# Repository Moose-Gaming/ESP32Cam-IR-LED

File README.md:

# ESP32Cam-IR-LED

***This Board makes your ESP32Cam see in the dark using 24 IR LEDs!***

In this repo, you will find the Gerber files required for ordering the PCB, as well as the KiCAD project files for editing the model (KiCAD 7.0 and later).
The archive folder holds all my previous .stl files.

The [**Wiki**](https://github.com/Moose-Gaming/ESP32Cam-IR-LED/wiki) should guide you through successfully ordering and assembling the PCB.

Check out [**my other projects**](https://github.com/Moose-Gaming/)!

***

# License
<br /> The ESP32Cam IR LED by MooseGaming is licensed under a <a rel="license" href="http://creativecommons.org/licenses/by-nc-sa/4.0/">Creative Commons Attribution-NonCommercial-ShareAlike 4.0 International License</a>.

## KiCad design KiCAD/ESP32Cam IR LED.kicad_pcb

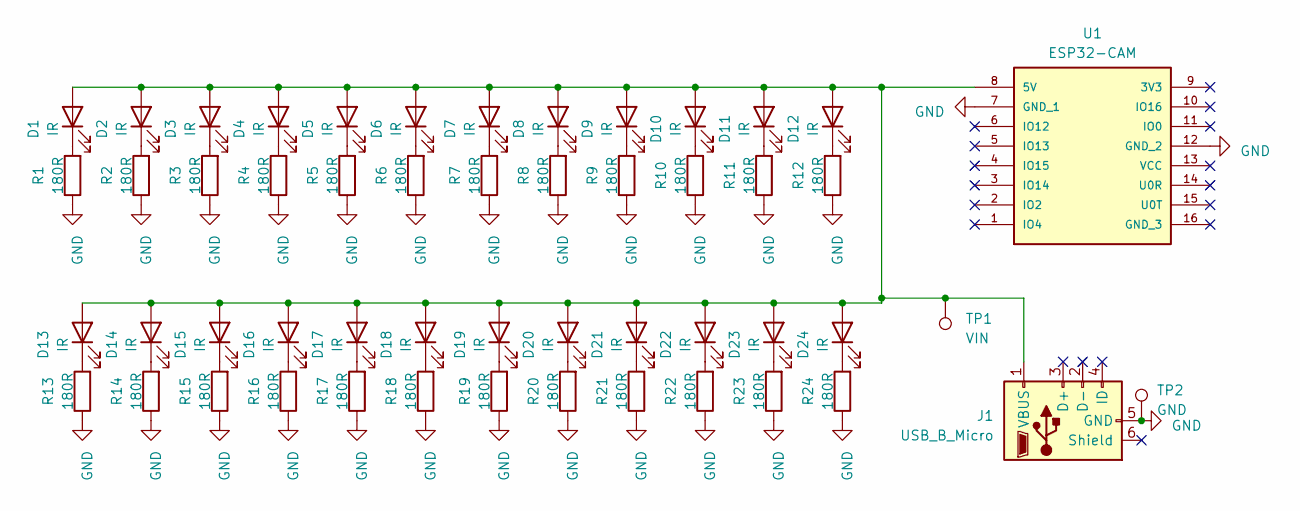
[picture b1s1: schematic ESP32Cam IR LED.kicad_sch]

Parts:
D1, D2, D3, D4, D5, D6, D7, D8, D9, D10, D11, D12, D13, D14, D15, D16, D17, D18, D19, D20, D21, D22, D23, D24: IR; LED_D3.0mm
J1: USB_B_Micro; USB_Micro-B_Wuerth_629105150521
R1, R2, R3, R4, R5, R6, R7, R8, R9, R10, R11, R12, R13, R14, R15, R16, R17, R18, R19, R20, R21, R22, R23, R24: 180R; R_0603_1608Metric
TP1: VIN; TestPoint_Pad_D2.0mm
TP2: GND; TestPoint_Pad_D2.0mm
U1: ESP32-CAM; MANUFACTURER_PART_NUMBER ESP32-CAM

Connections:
GND: J1.5 (GND), R1.1, R2.1, R3.1, R4.1, R5.1, R6.1, R7.1, R8.1, R9.1, R10.1, R11.1, R12.1, R13.1, R14.1, R15.1, R16.1, R17.1, R18.1, R19.1, R20.1, R21.1, R22.1, R23.1, R24.1, TP2.1, U1.7 (GND_1), U1.12 (GND_2)
unnamed: D1.2 (A), D2.2 (A), D3.2 (A), D4.2 (A), D5.2 (A), D6.2 (A), D7.2 (A), D8.2 (A), D9.2 (A), D10.2 (A), D11.2 (A), D12.2 (A), D13.2 (A), D14.2 (A), D15.2 (A), D16.2 (A), D17.2 (A), D18.2 (A), D19.2 (A), D20.2 (A), D21.2 (A), D22.2 (A), D23.2 (A), D24.2 (A), J1.1 (VBUS), TP1.1, U1.8 (5V)
unnamed: D1.1 (K), R1.2
unnamed: D2.1 (K), R2.2
unnamed: D3.1 (K), R3.2
unnamed: D4.1 (K), R4.2
unnamed: D5.1 (K), R5.2
unnamed: D6.1 (K), R6.2
unnamed: D7.1 (K), R7.2
unnamed: D8.1 (K), R8.2
unnamed: D9.1 (K), R9.2
unnamed: D10.1 (K), R10.2
unnamed: D11.1 (K), R11.2
unnamed: D12.1 (K), R12.2
unnamed: D13.1 (K), R13.2
unnamed: D14.1 (K), R14.2
unnamed: D15.1 (K), R15.2
unnamed: D16.1 (K), R16.2
unnamed: D17.1 (K), R17.2
unnamed: D18.1 (K), R18.2
unnamed: D19.1 (K), R19.2
unnamed: D20.1 (K), R20.2
unnamed: D21.1 (K), R21.2
unnamed: D22.1 (K), R22.2
unnamed: D23.1 (K), R23.2
unnamed: D24.1 (K), R24.2

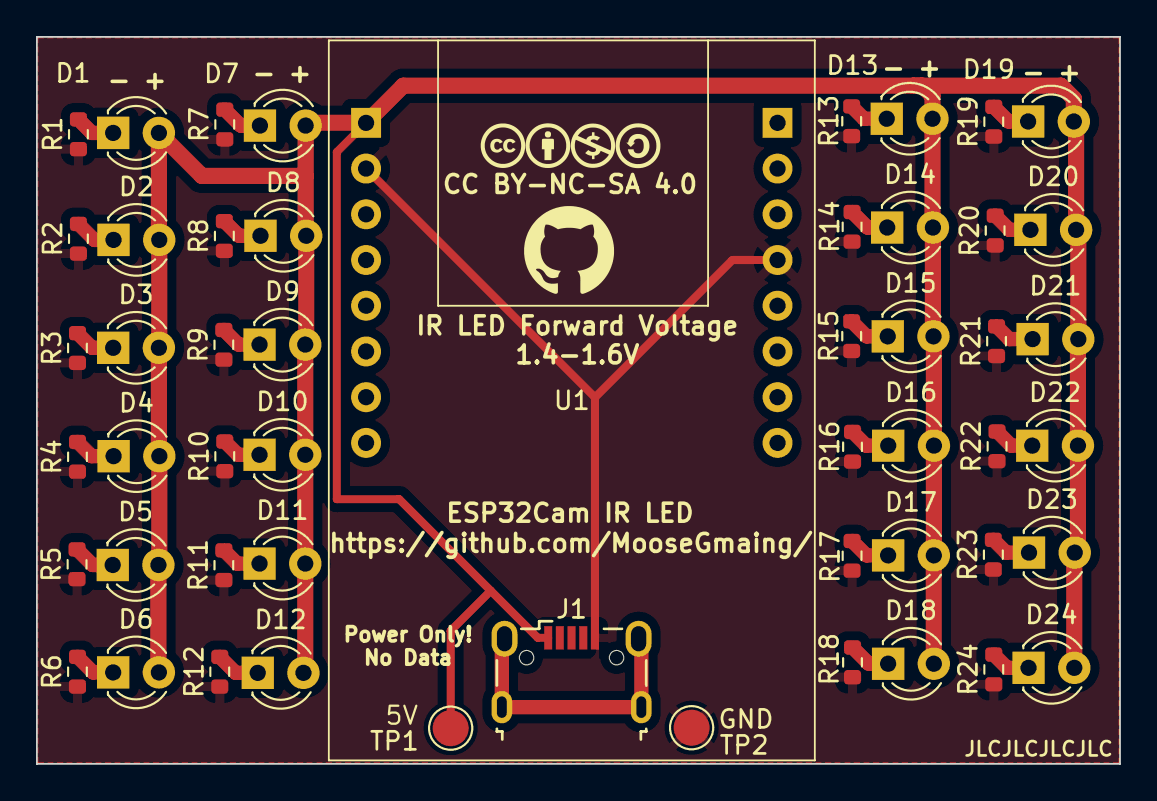
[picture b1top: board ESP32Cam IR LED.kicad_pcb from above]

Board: 2 copper layers, 60.2 x 40.4 mm, 52 parts (0 on the bottom side), 26 nets.

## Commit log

2023-09-27 Setting up Readme.md
2023-09-27 Create Images folder
2023-09-27 Added 3D Render
2023-09-27 Created Gerbers folder
2023-09-27 Added Gerber files
2023-09-27 Add home wiki images
2024-08-05 Update links

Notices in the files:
KiCAD/ESP32Cam IR LED.kicad_pcb:
CC BY-NC-SA 4.0
